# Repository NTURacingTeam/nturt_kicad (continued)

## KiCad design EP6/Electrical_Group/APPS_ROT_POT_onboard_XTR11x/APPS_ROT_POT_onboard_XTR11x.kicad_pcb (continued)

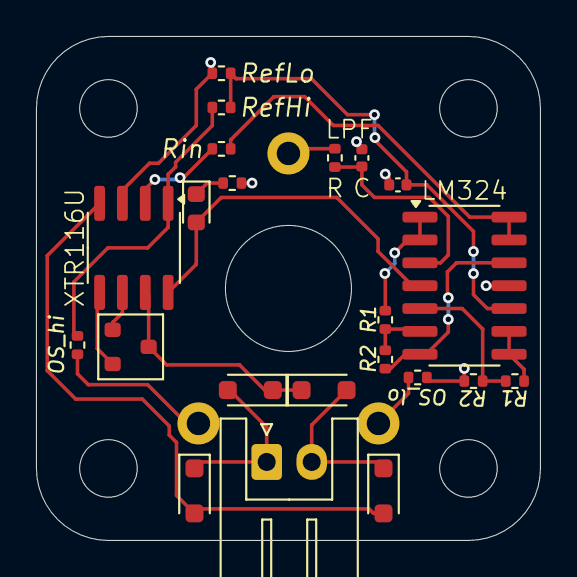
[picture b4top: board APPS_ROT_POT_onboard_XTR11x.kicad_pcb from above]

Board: 2 copper layers, 28.0 x 28.0 mm, 27 parts (1 on the bottom side), 22 nets.

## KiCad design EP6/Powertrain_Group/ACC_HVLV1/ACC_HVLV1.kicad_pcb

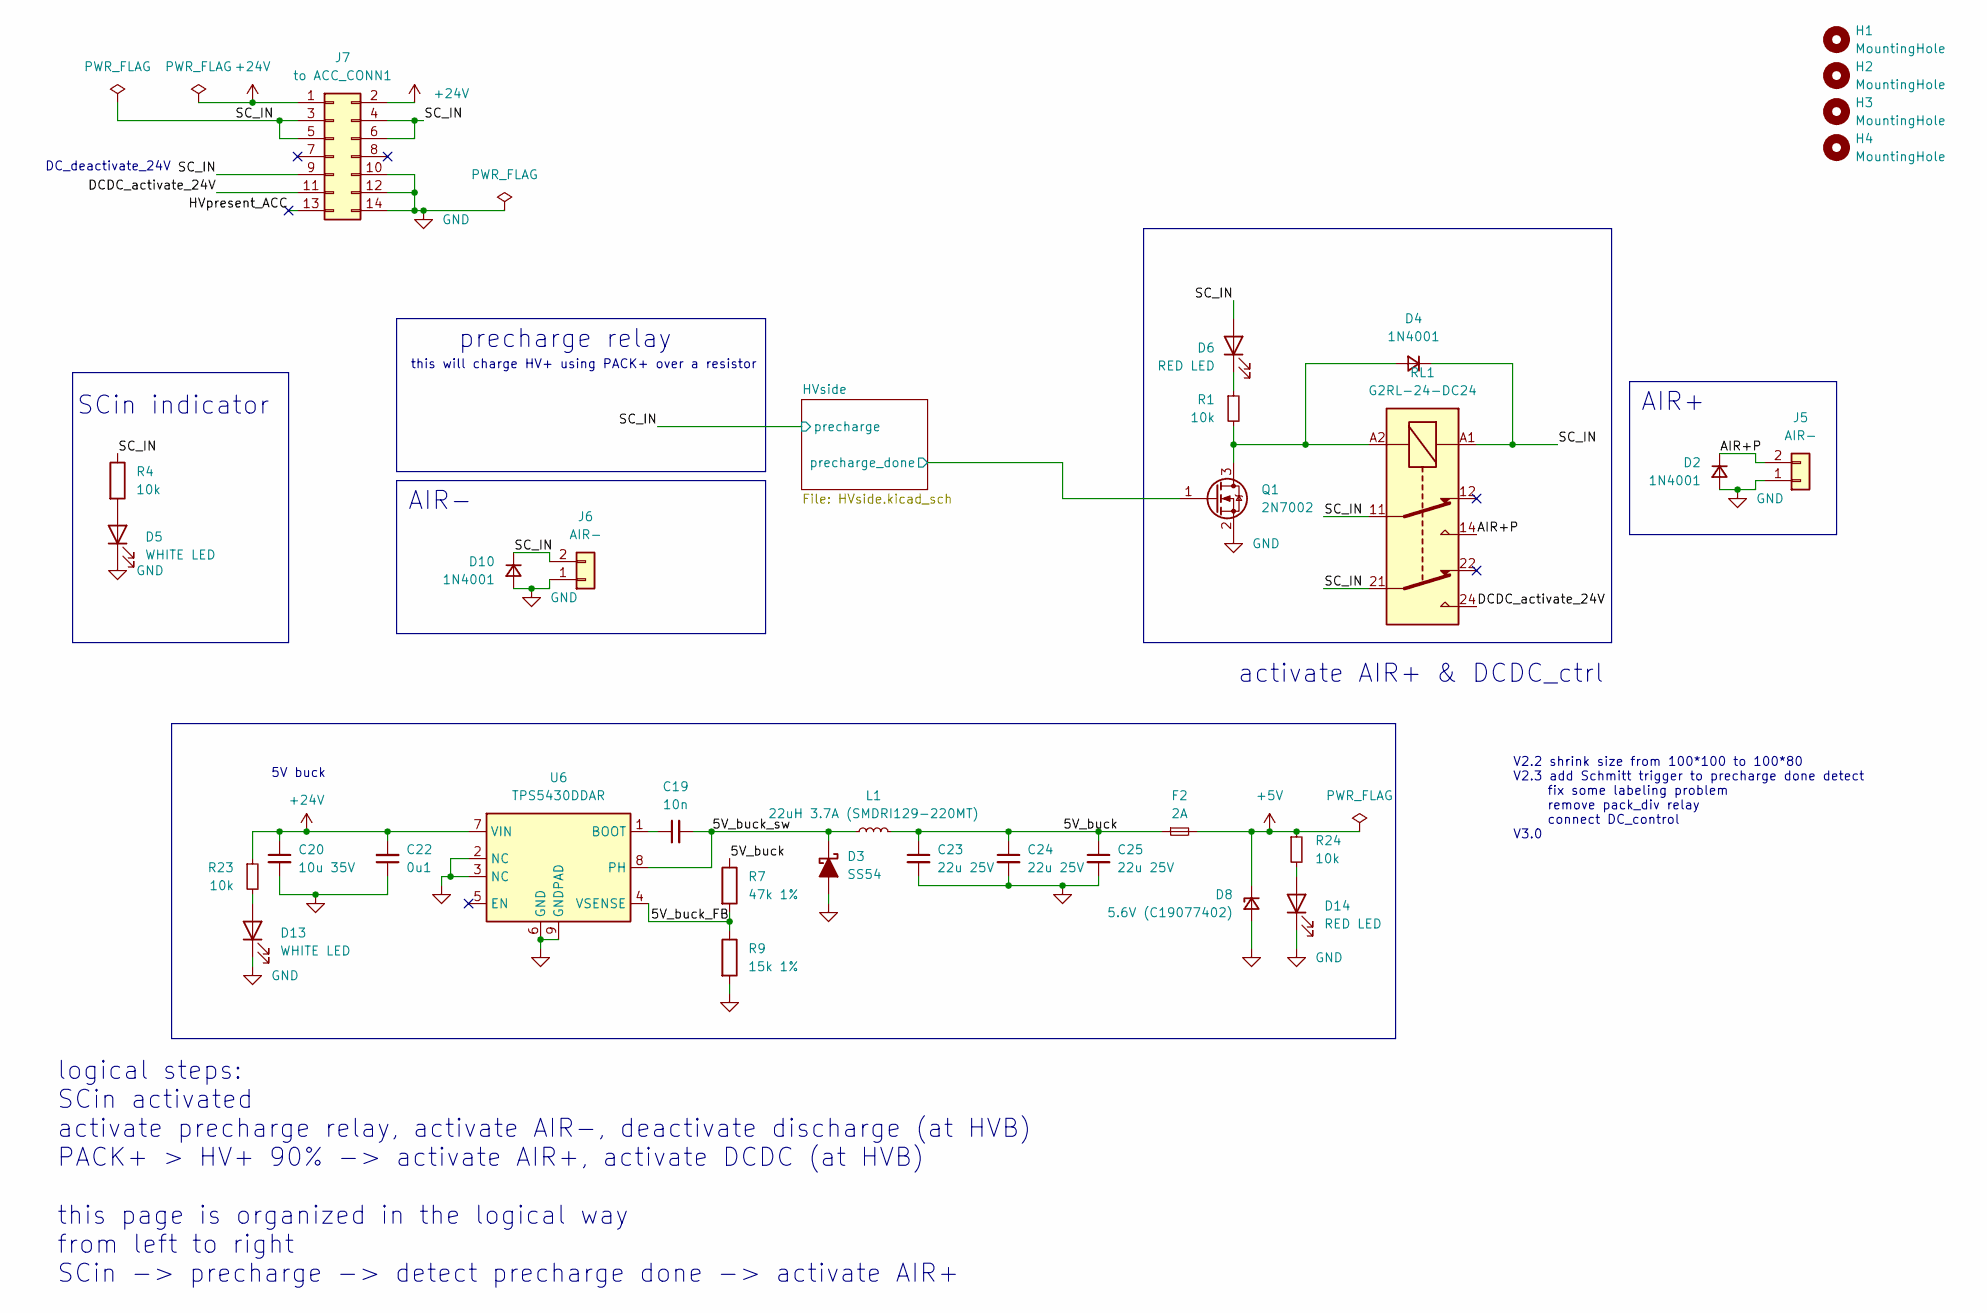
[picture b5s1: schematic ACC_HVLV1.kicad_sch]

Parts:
C19: 10n; C_0603_1608Metric
C20: 10u 35V; C_1206_3216Metric
C22: 0u1; C_0603_1608Metric
C23, C24, C25: 22u 25V; C_1206_3216Metric
D2, D4, D10: 1N4001; D_SOD-123F
D3: SS54; D_SMA
D5, D13: WHITE LED; LED_0805_2012Metric_Pad1.15x1.40mm_HandSolder
D6, D14: RED LED; LED_0805_2012Metric_Pad1.15x1.40mm_HandSolder
D8: 5.6V (C19077402); D_SOD-123
F2: 2A; Fuse_1206_3216Metric
H1, H2, H3, H4: MountingHole; MountingHole_3.2mm_M3
J5, J6: AIR-; JST_VH_B2P-VH-B_1x02_P3.96mm_Vertical
J7: to ACC_CONN1; IDC-Header_2x07_P2.54mm_Vertical
L1: 22uH 3.7A (SMDRI129-220MT); L_Bourns_SRR1260
Q1: 2N7002; SOT-23
R1: 10k; R_0603_1608Metric_Pad0.98x0.95mm_HandSolder
R4: 10k; R_0603_1608Metric
R7: 47k 1%; R_0603_1608Metric
R9: 15k 1%; R_0603_1608Metric
R23, R24: 10k; R_0805_2012Metric_Pad1.20x1.40mm_HandSolder
RL1: G2RL-24-DC24; Relay_DPDT_Omron_G2RL-2
U6: TPS5430DDAR; TI_SO-PowerPAD-8_ThermalVias

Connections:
+5V: D8.1 (K), F2.2, R24.1; also elsewhere on the board
+24V: C20.1, C22.2, J7.1, J7.2, R23.1, U6.7 (VIN)
/5V_buck: C23.1, C24.1, C25.1, F2.1, L1.2, R7.1
/5V_buck_FB: R7.2, R9.1, U6.4 (VSENSE)
/5V_buck_sw: C19.2, D3.1 (K), L1.1, U6.8 (PH)
/AIR+P: D2.1 (K), J5.2, RL1.14
/DCDC_activate_24V: J7.11, RL1.24
/HVpresent_ACC: J7.13
/HVside/precharge_done: Q1.1 (G); also elsewhere on the board
/SC_IN: D4.1 (K), D6.2 (A), D10.1 (K), J6.2, J7.3, J7.4, J7.5, J7.6, J7.9, R4.1, RL1.11, RL1.21, RL1.A1; also elsewhere on the board
GND: C20.2, C22.1, C23.2, C24.2, C25.2, D2.2 (A), D3.2 (A), D5.1 (K), D8.2 (A), D10.2 (A), D13.1 (K), D14.1 (K), J5.1, J6.1, J7.10, J7.12, J7.14, Q1.2 (S), R9.2, U6.2 (NC), U6.3 (NC), U6.6 (GND), U6.9 (GNDPAD); also elsewhere on the board
unnamed: D4.2 (A), Q1.3 (D), R1.2, RL1.A2
unnamed: D5.2 (A), R4.2
unnamed: D6.1 (K), R1.1
unnamed: D13.2 (A), R23.2
unnamed: D14.2 (A), R24.2
unnamed: C19.1, U6.1 (BOOT)

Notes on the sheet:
AIR-
AIR+
V2.2 shrink size from 100*100 to 100*80 V2.3 add Schmitt trigger to precharge done detect fix some labeling problem remove pack_div relay connect DC_control V3.0
5V buck
SCin indicator
this will charge HV+ using PACK+ over a resistor
DC_deactivate_24V
activate AIR+ & DCDC_ctrl
precharge relay
logical steps: SCin activated activate precharge relay, activate AIR-, deactivate discharge (at HVB) PACK+ > HV+ 90% -> activate AIR+, activate DCDC (at HVB) this page is organized in the logical way from left to right SCin -> precharge -> detect precharge done -> activate AIR+

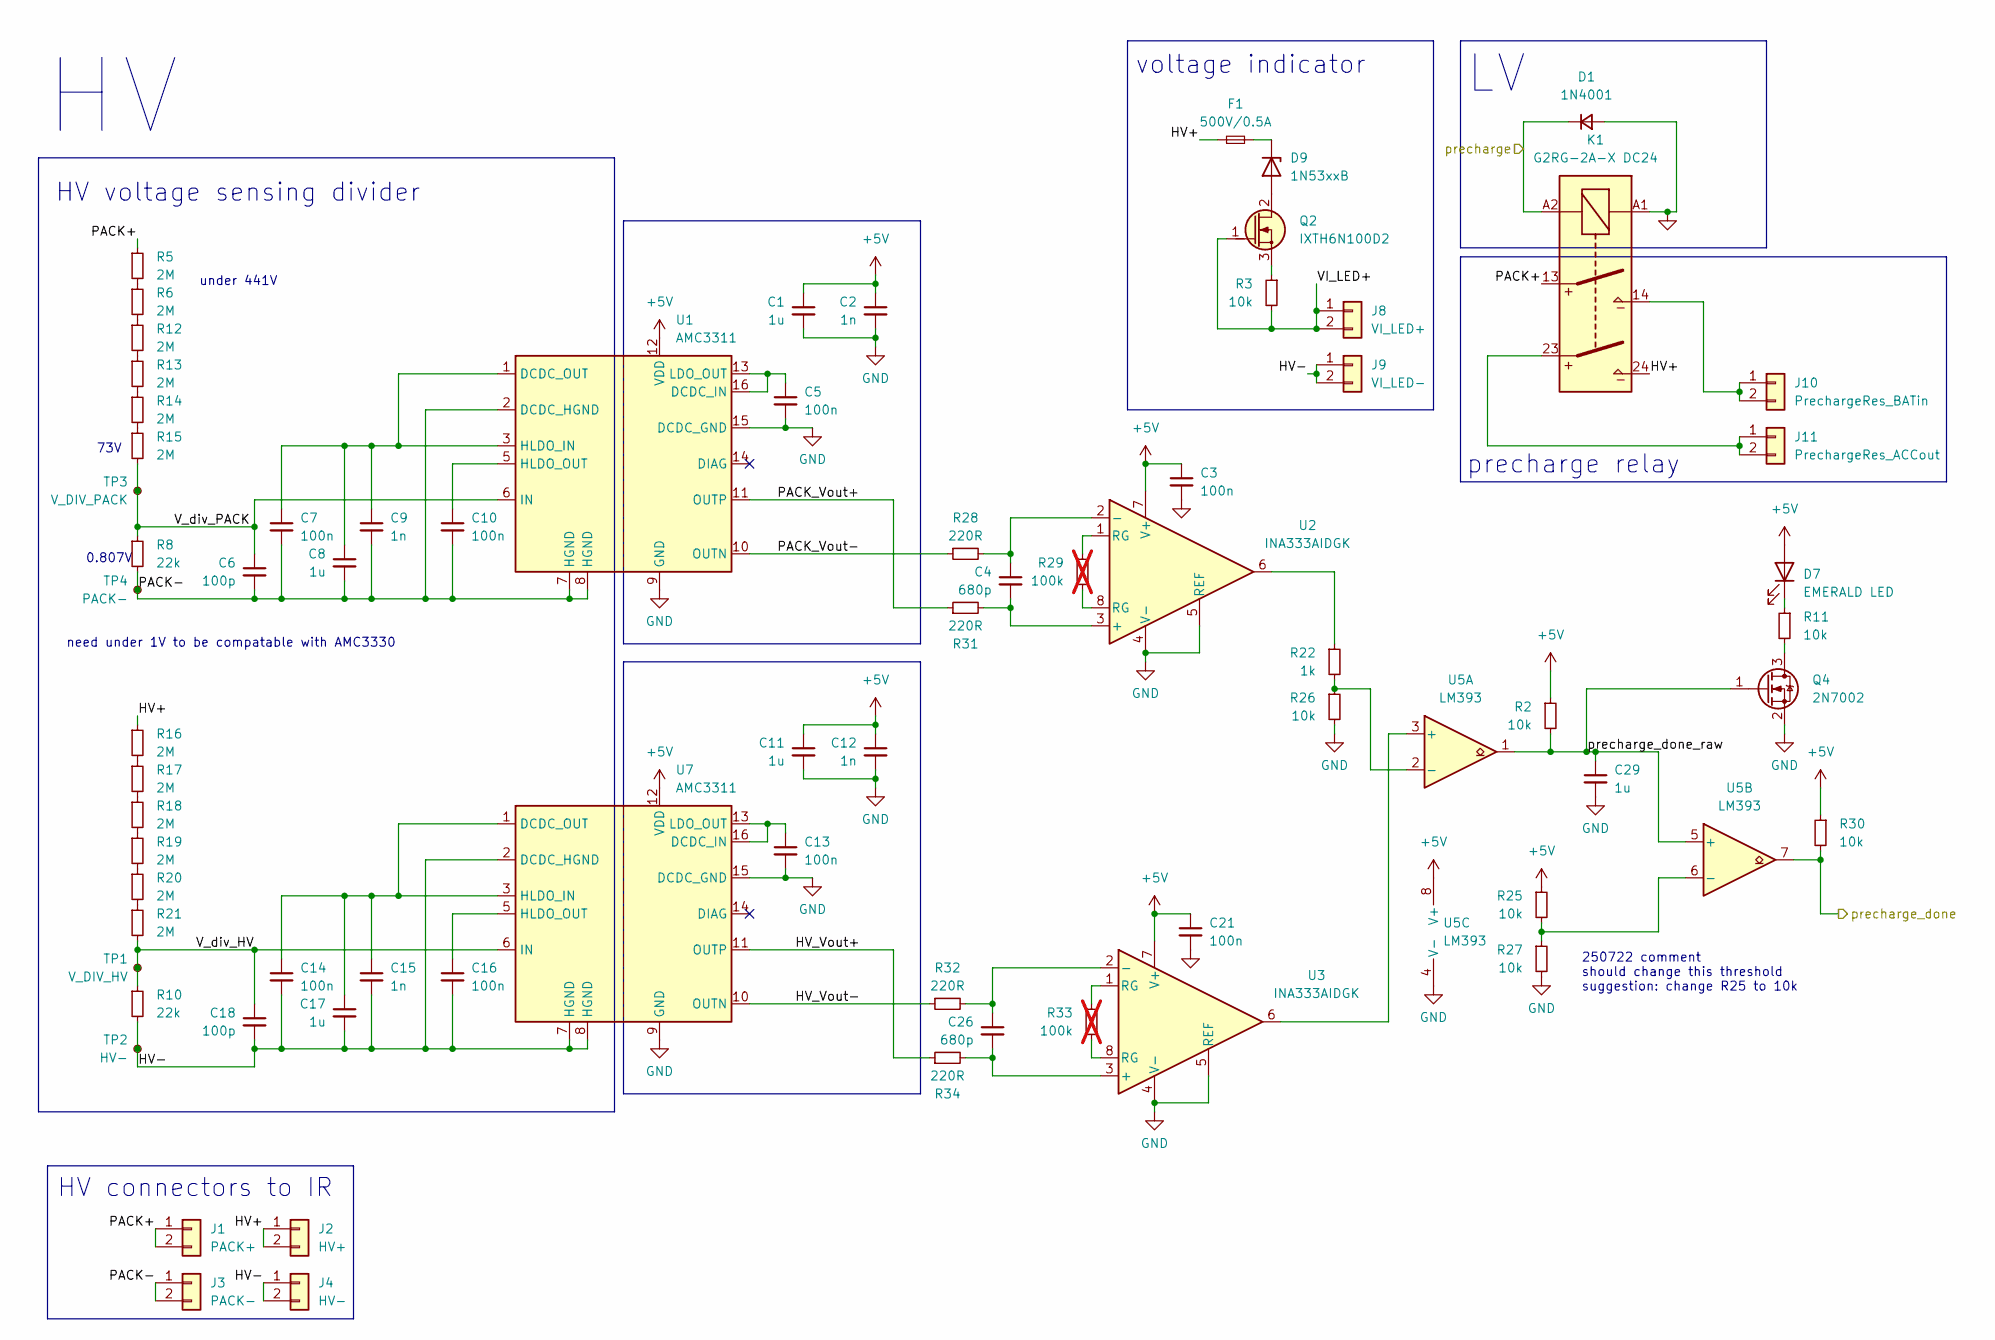
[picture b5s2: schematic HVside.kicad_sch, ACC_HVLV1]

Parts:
C1, C8, C11, C17, C29: 1u; C_0603_1608Metric
C2, C9, C12, C15: 1n; C_0603_1608Metric
C3, C21: 100n; C_0402_1005Metric
C4, C26: 680p; C_0402_1005Metric
C5, C7, C10, C13, C14, C16: 100n; C_0603_1608Metric
C6, C18: 100p; C_0603_1608Metric
D1: 1N4001; D_SOD-123F
D7: EMERALD LED; LED_0805_2012Metric_Pad1.15x1.40mm_HandSolder
D9: 1N53xxB; D_DO-201_P15.24mm_Horizontal
F1: 500V/0.5A; 65600001009; Rating W
J1: PACK+; HRS_DF33C-2P-3.3DSA
J2: HV+; HRS_DF33C-2P-3.3DSA
J3: PACK-; HRS_DF33C-2P-3.3DSA
J4: HV-; HRS_DF33C-2P-3.3DSA
J8: VI_LED+; HRS_DF33C-2P-3.3DSA
J9: VI_LED-; HRS_DF33C-2P-3.3DSA
J10: PrechargeRes_BATin; HRS_DF33C-2P-3.3DSA
J11: PrechargeRes_ACCout; HRS_DF33C-2P-3.3DSA
K1: G2RG-2A-X DC24; Relay_DPST_Omron_G2RL-2A
Q2: IXTH6N100D2; TO-247-3_Vertical
Q4: 2N7002; SOT-23
R2, R11, R25, R26, R27, R30: 10k; R_0603_1608Metric_Pad0.98x0.95mm_HandSolder
R3: 10k; R_0805_2012Metric_Pad1.20x1.40mm_HandSolder
R5, R6, R12, R13, R14, R15, R16, R17, R18, R19, R20, R21: 2M; R_0805_2012Metric_Pad1.20x1.40mm_HandSolder
R8, R10: 22k; R_0805_2012Metric_Pad1.20x1.40mm_HandSolder
R22: 1k; R_0603_1608Metric_Pad0.98x0.95mm_HandSolder
R28, R31, R32, R34: 220R; R_0402_1005Metric
R29, R33: 100k; R_0402_1005Metric; not fitted
TP1: V_DIV_HV; TestPoint_Pad_D2.0mm
TP2: HV-; TestPoint_Pad_D2.0mm
TP3: V_DIV_PACK; TestPoint_Pad_D2.0mm
TP4: PACK-; TestPoint_Pad_D2.0mm
U1, U7: AMC3311; SOIC-16W_7.5x10.3mm_P1.27mm
U2, U3: INA333AIDGK; MSOP-8_3x3mm_P0.65mm
U5: LM393; SOIC-8_3.9x4.9mm_P1.27mm

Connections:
+5V: C1.1, C2.1, C3.1, C11.1, C12.1, C21.1, D7.2 (A), R2.1, R25.1, R30.1, U1.12 (VDD), U2.7 (V+), U3.7 (V+), U5.8 (V+), U7.12 (VDD); also elsewhere on the board
/HVside/HV+: F1.2, J2.1, J2.2, K1.24, R16.1
/HVside/HV-: C14.2, C15.2, C16.2, C17.2, C18.2, J4.1, J4.2, J9.1, J9.2, R10.2, TP2.1, U7.2 (DCDC_HGND), U7.7 (HGND), U7.8 (HGND)
/HVside/HV_Vout+: R34.1, U7.11 (OUTP)
/HVside/HV_Vout-: R32.1, U7.10 (OUTN)
/HVside/PACK+: J1.1, J1.2, K1.13, R5.1
/HVside/PACK-: C6.2, C7.2, C8.2, C9.2, C10.2, J3.1, J3.2, R8.2, TP4.1, U1.2 (DCDC_HGND), U1.7 (HGND), U1.8 (HGND)
/HVside/PACK_Vout+: R31.1, U1.11 (OUTP)
/HVside/PACK_Vout-: R28.1, U1.10 (OUTN)
/HVside/VI_LED+: J8.1, J8.2, Q2.1 (G), R3.2
/HVside/V_div_HV: C18.1, R10.1, R21.2, TP1.1, U7.6 (IN)
/HVside/V_div_PACK: C6.1, R8.1, R15.2, TP3.1, U1.6 (IN)
/HVside/precharge_done: R30.2, U5.7; also elsewhere on the board
/HVside/precharge_done_raw: C29.1, Q4.1 (G), R2.2, U5.1, U5.5 (+)
/SC_IN: D1.1 (K), K1.A2; also elsewhere on the board
GND: C1.2, C2.2, C3.2, C5.2, C11.2, C12.2, C13.2, C21.2, C29.2, D1.2 (A), K1.A1, Q4.2 (S), R26.2, R27.2, U1.9 (GND), U1.15 (DCDC_GND), U2.4 (V-), U2.5 (REF), U3.4 (V-), U3.5 (REF), U5.4 (V-), U7.9 (GND), U7.15 (DCDC_GND); also elsewhere on the board
unnamed: D7.1 (K), R11.1
unnamed: D9.2 (A), Q2.2 (D)
unnamed: D9.1 (K), F1.1
unnamed: J10.1, J10.2, K1.14
unnamed: J11.1, J11.2, K1.23
unnamed: Q2.3 (S), R3.1
unnamed: Q4.3 (D), R11.2
unnamed: R5.2, R6.1
unnamed: R6.2, R12.1
unnamed: R12.2, R13.1
unnamed: R13.2, R14.1
unnamed: R14.2, R15.1
unnamed: R16.2, R17.1
unnamed: R17.2, R18.1
unnamed: R18.2, R19.1
unnamed: R19.2, R20.1
unnamed: R20.2, R21.1
unnamed: R22.1, U2.6
unnamed: R29.1, U2.8 (RG)
unnamed: R29.2, U2.1 (RG)
unnamed: R33.1, U3.8 (RG)
unnamed: R33.2, U3.1 (RG)
unnamed: C5.1, U1.13 (LDO_OUT), U1.16 (DCDC_IN)
unnamed: C7.1, C8.1, C9.1, U1.1 (DCDC_OUT), U1.3 (HLDO_IN)
unnamed: C10.1, U1.5 (HLDO_OUT)
unnamed: C4.2, R31.2, U2.3 (+)
unnamed: C4.1, R28.2, U2.2 (-)
unnamed: C26.2, R34.2, U3.3 (+)
unnamed: C26.1, R32.2, U3.2 (-)
unnamed: U3.6, U5.3 (+)
unnamed: R22.2, R26.1, U5.2 (-)
unnamed: R25.2, R27.1, U5.6 (-)
unnamed: C13.1, U7.13 (LDO_OUT), U7.16 (DCDC_IN)
unnamed: C14.1, C15.1, C17.1, U7.1 (DCDC_OUT), U7.3 (HLDO_IN)
unnamed: C16.1, U7.5 (HLDO_OUT)

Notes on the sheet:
250722 comment should change this threshold suggestion: change R25 to 10k
voltage indicator
HV voltage sensing divider
HV connectors to IR
under 441V
73V
need under 1V to be compatable with AMC3330
precharge relay
0.807V

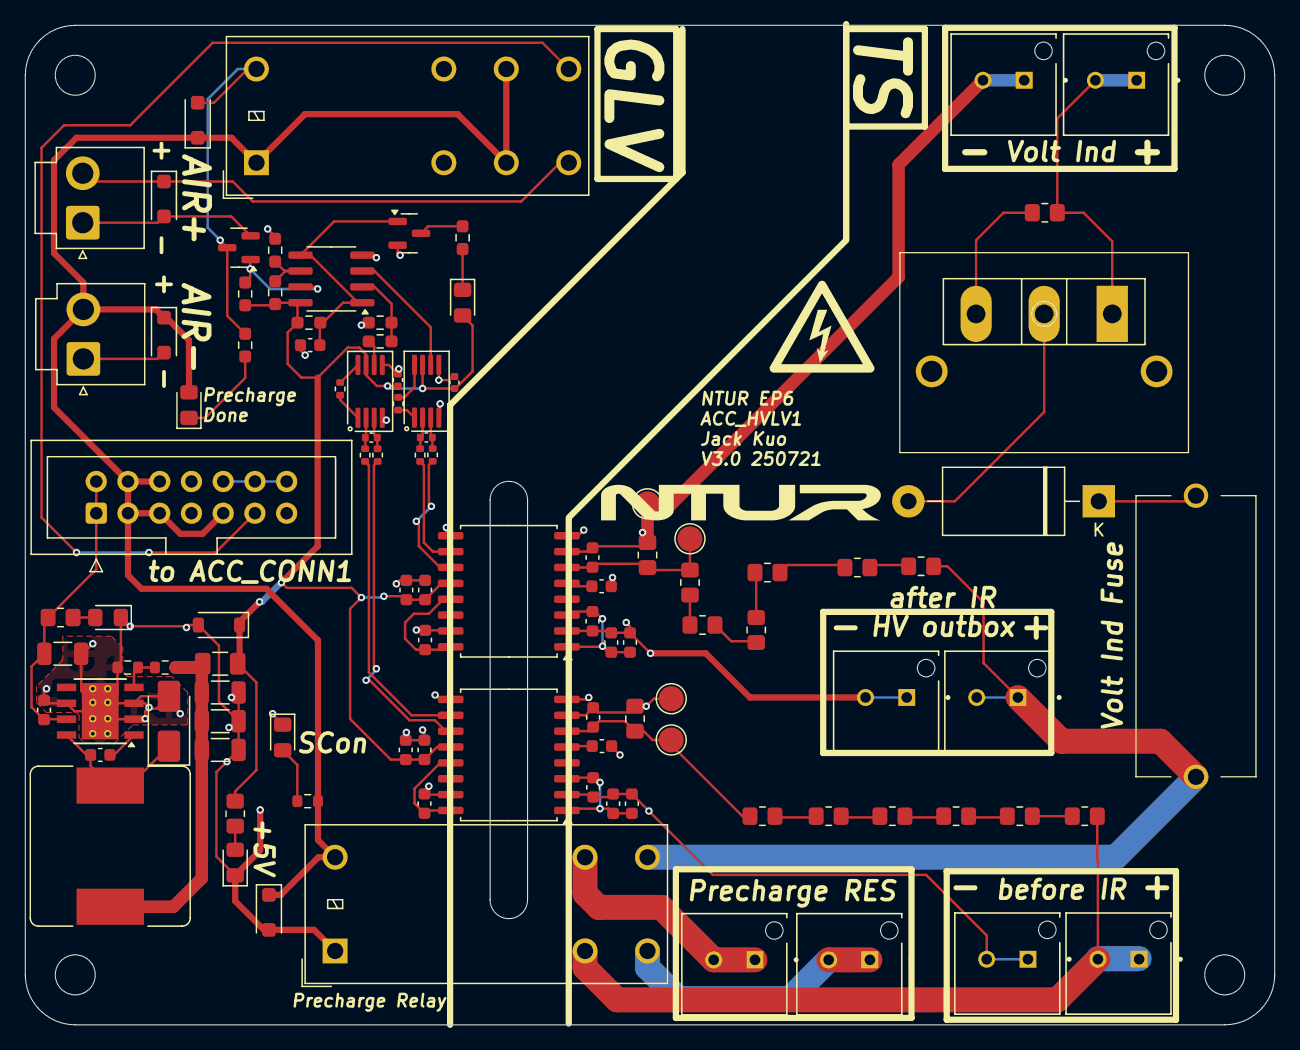
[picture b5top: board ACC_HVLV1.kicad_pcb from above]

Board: 2 copper layers, 100.0 x 80.0 mm, 106 parts (0 on the bottom side), 63 nets.

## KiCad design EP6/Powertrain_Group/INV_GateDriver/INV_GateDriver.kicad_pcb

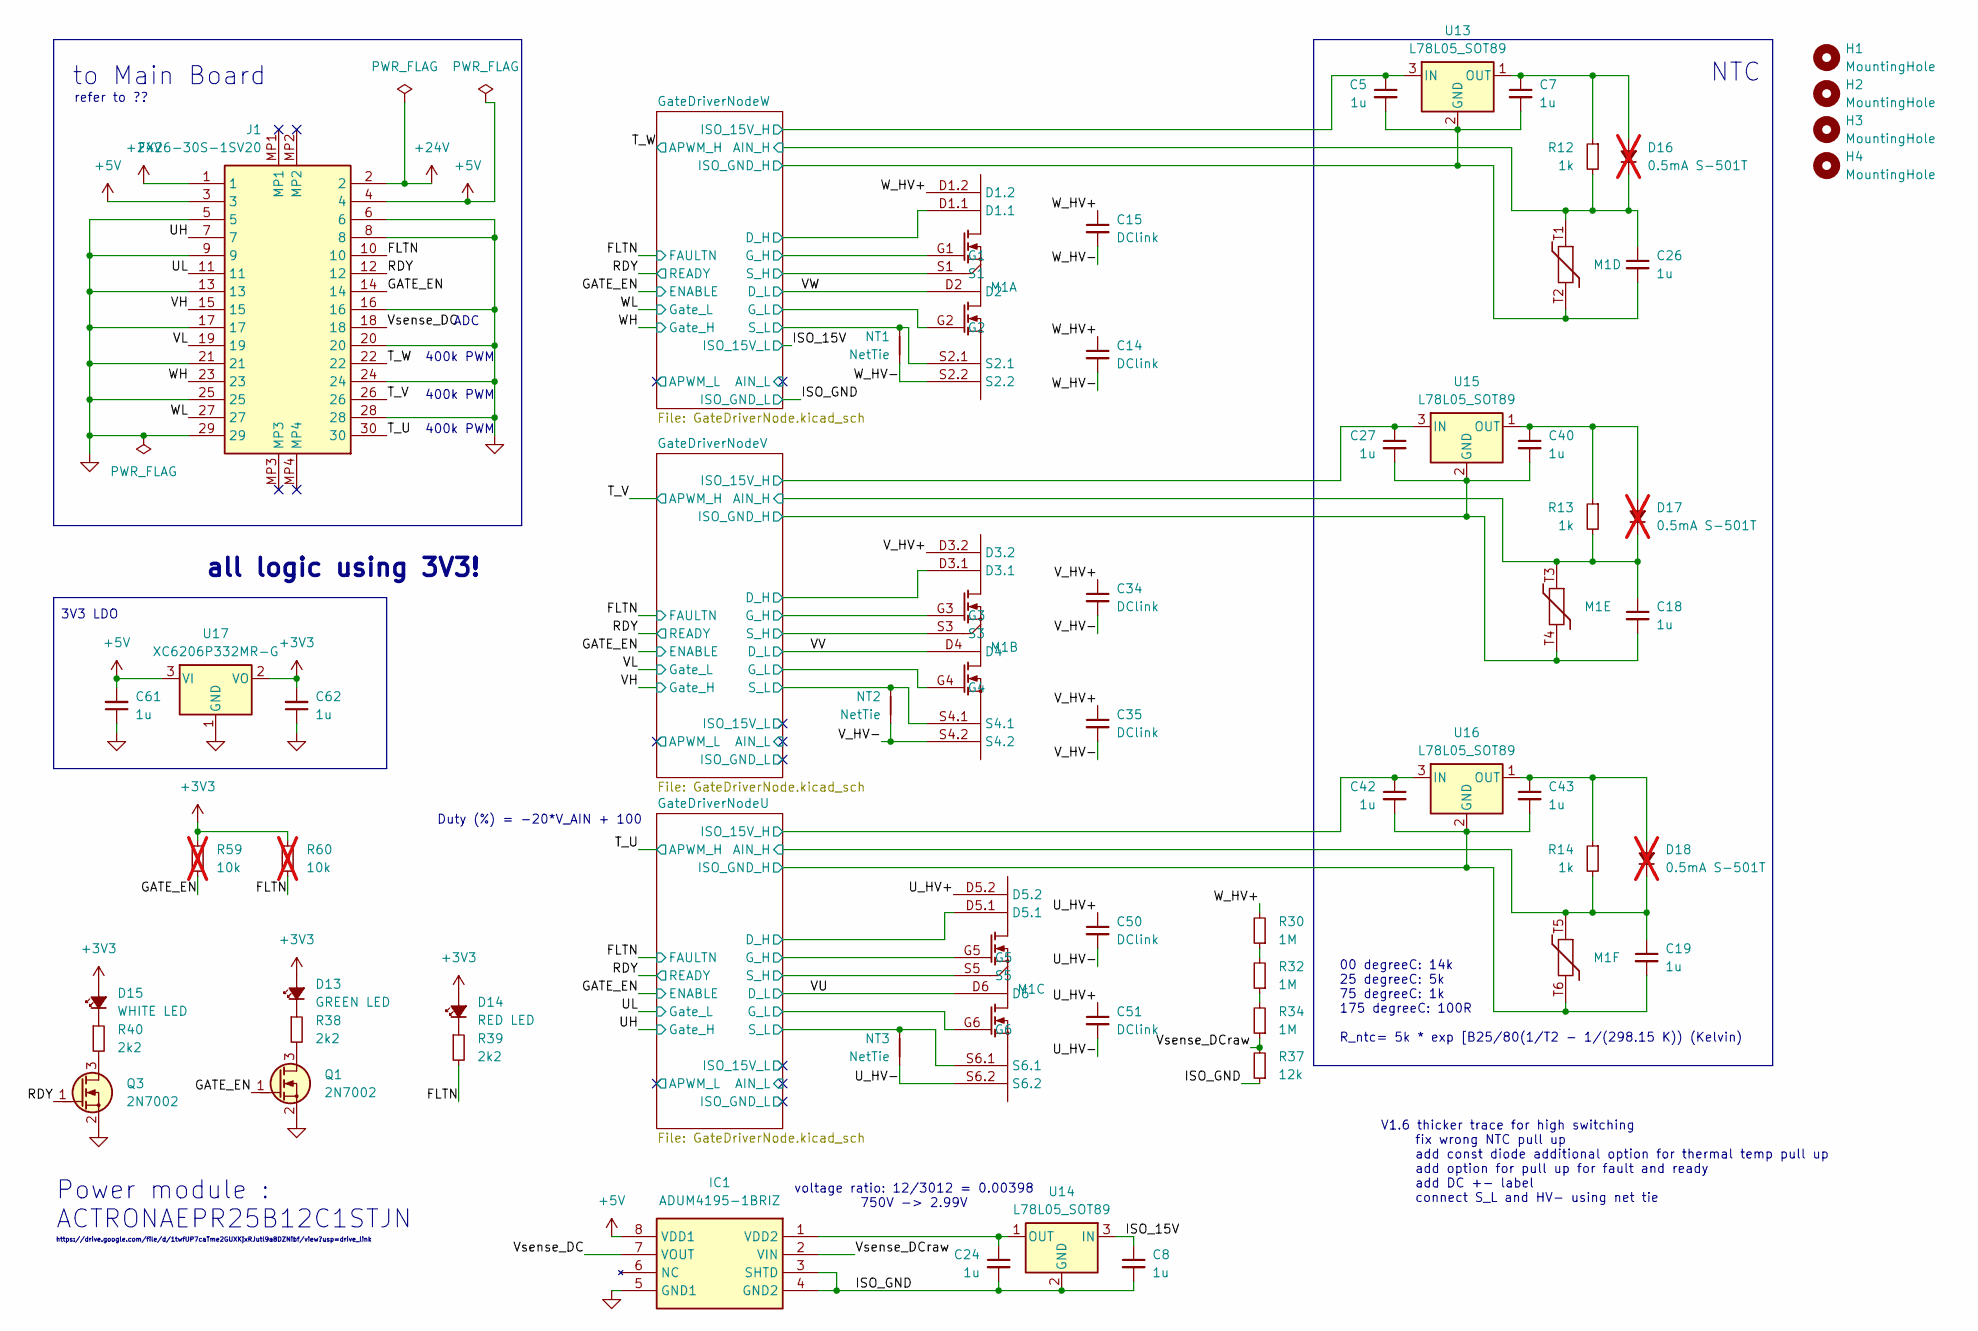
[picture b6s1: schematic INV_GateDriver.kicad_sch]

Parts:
C5, C7, C8, C18, C19, C24, C26, C27, C40, C42, C43: 1u; C_0603_1608Metric
C14, C15, C34, C35, C50, C51: DClink; B58035U5205M062
C61, C62: 1u; C_0402_1005Metric
D13: GREEN LED; LED_0805_2012Metric
D14: RED LED; LED_0805_2012Metric
D15: WHITE LED; LED_0805_2012Metric
D16, D17, D18: 0.5mA S-501T; D_1206_3216Metric; not fitted
H1, H2, H3, H4: MountingHole; MountingHole_3.2mm_M3
IC1: ADUM4195-1BRIZ; SOIC127P1031X265-8N; Manufacturer_Part_Number ADUM4195-1BRIZ; Mouser Part Number 584-ADUM4195-1BRIZ
J1: FX26-30S-1SV20; FX2630S1SV20; Mouser Part Number 798-FX2630S1SV20
M1: InverterSiCModule_HybridPack
NT1, NT2, NT3: NetTie; NetTie-2_SMD_Pad2.0mm
Q1, Q3: 2N7002; SOT-23
R12, R13, R14: 1k; R_0603_1608Metric
R30, R32, R34: 1M; R_1206_3216Metric
R37: 12k; R_0805_2012Metric
R38, R39, R40: 2k2; R_0402_1005Metric
R59, R60: 10k; R_0402_1005Metric; not fitted
U13, U14, U15, U16: L78L05_SOT89; SOT-89-3
U17: XC6206P332MR-G; SOT-23-3

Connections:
+3V3: C62.2, D13.2 (A), D14.2 (A), D15.2 (A), R59.1, R60.1, U17.2 (VO); also elsewhere on the board
+5V: C61.2, IC1.8 (VDD1), J1.3, J1.4, U17.3 (VI)
+24V: J1.1, J1.2; also elsewhere on the board
/FLTN: J1.10, R39.2, R60.2; also elsewhere on the board
/GATE_EN: J1.14, Q1.1 (G), R59.2; also elsewhere on the board
/GateDriverNodeU/0V_H: C19.2, C42.2, C43.2, M1.S5, M1.T6, U16.2 (GND); also elsewhere on the board
/GateDriverNodeU/0V_L: M1.S6.1, NT3.2; also elsewhere on the board
/GateDriverNodeU/+V_H: C42.1, U16.3 (IN); also elsewhere on the board
/GateDriverNodeU/AIN_H: C19.1, D18.1 (K), M1.T5, R14.2; also elsewhere on the board
/GateDriverNodeU/D_H: M1.D5.1; also elsewhere on the board
/GateDriverNodeU/G_H: M1.G5; also elsewhere on the board
/GateDriverNodeU/G_L: M1.G6; also elsewhere on the board
/GateDriverNodeV/0V_H: C18.2, C27.2, C40.2, M1.S3, M1.T4, U15.2 (GND); also elsewhere on the board
/GateDriverNodeV/0V_L: M1.S4.1, NT2.2; also elsewhere on the board
/GateDriverNodeV/+V_H: C27.1, U15.3 (IN); also elsewhere on the board
/GateDriverNodeV/AIN_H: C18.1, D17.1 (K), M1.T3, R13.2; also elsewhere on the board
/GateDriverNodeV/D_H: M1.D3.1; also elsewhere on the board
/GateDriverNodeV/G_H: M1.G3; also elsewhere on the board
/GateDriverNodeV/G_L: M1.G4; also elsewhere on the board
/GateDriverNodeW/0V_H: C5.2, C7.2, C26.2, M1.S1, M1.T2, U13.2 (GND); also elsewhere on the board
/GateDriverNodeW/+V_H: C5.1, U13.3 (IN); also elsewhere on the board
/GateDriverNodeW/AIN_H: C26.1, D16.1 (K), M1.T1, R12.2; also elsewhere on the board
/GateDriverNodeW/D_H: M1.D1.1; also elsewhere on the board
/GateDriverNodeW/G_H: M1.G1; also elsewhere on the board
/GateDriverNodeW/G_L: M1.G2; also elsewhere on the board
/ISO_15V: C8.1, U14.3 (IN); also elsewhere on the board
/ISO_GND: C8.2, C24.2, IC1.3 (SHTD), IC1.4 (GND2), M1.S2.1, NT1.2, R37.1, U14.2 (GND); also elsewhere on the board
/RDY: J1.12, Q3.1 (G); also elsewhere on the board
/T_U: J1.30; also elsewhere on the board
/T_V: J1.26; also elsewhere on the board
/T_W: J1.22; also elsewhere on the board
/UH: J1.7; also elsewhere on the board
/UL: J1.11; also elsewhere on the board
/U_HV+: C50.1, C51.1, M1.D5.2
/U_HV-: C50.2, C51.2, M1.S6.2, NT3.1
/VH: J1.15; also elsewhere on the board
/VL: J1.19; also elsewhere on the board
/VU: M1.D6; also elsewhere on the board
/VV: M1.D4; also elsewhere on the board
/VW: M1.D2; also elsewhere on the board
/V_HV+: C34.1, C35.1, M1.D3.2
/V_HV-: C34.2, C35.2, M1.S4.2, NT2.1
/Vsense_DC: IC1.7 (VOUT), J1.18
/Vsense_DCraw: IC1.2 (VIN), R34.1, R37.2
/WH: J1.23; also elsewhere on the board
/WL: J1.27; also elsewhere on the board
/W_HV+: C14.1, C15.1, M1.D1.2, R30.2
/W_HV-: C14.2, C15.2, M1.S2.2, NT1.1
GND: C61.1, C62.1, IC1.5 (GND1), J1.5, J1.6, J1.8, J1.9, J1.13, J1.16, J1.17, J1.20, J1.21, J1.24, J1.25, J1.28, J1.29, Q1.2 (S), Q3.2 (S), U17.1 (GND); also elsewhere on the board
unnamed: D13.1 (K), R38.1
unnamed: D14.1 (K), R39.1
unnamed: D15.1 (K), R40.1
unnamed: C7.1, D16.2 (A), R12.1, U13.1 (OUT)
unnamed: C40.1, D17.2 (A), R13.1, U15.1 (OUT)
unnamed: C43.1, D18.2 (A), R14.1, U16.1 (OUT)
unnamed: C24.1, IC1.1 (VDD2), U14.1 (OUT)
unnamed: Q1.3 (D), R38.2
unnamed: Q3.3 (D), R40.2
unnamed: R30.1, R32.2
unnamed: R32.1, R34.2

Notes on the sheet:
Power module : ACTRONAEPR25B12C1STJN
NTC
all logic using 3V3!
V1.6 thicker trace for high switching fix wrong NTC pull up add const diode additional option for thermal temp pull up add option for pull up for fault and ready add DC +- label connect S_L and HV- using net tie
Duty (%) = -20*V_AIN + 100
400k PWM
refer to ??
to Main Board
ADC
3V3 LDO
00 degreeC: 14k 25 degreeC: 5k 75 degreeC: 1k 175 degreeC: 100R R_ntc= 5k * exp [B25/80(1/T2 - 1/(298.15 K)) (Kelvin)
voltage ratio: 12/3012 = 0.00398 750V -> 2.99V
https://drive.google.com/file/d/1twfUP7caTme2GUXKjxRJutl9a8DZNibf/view?usp=drive_link

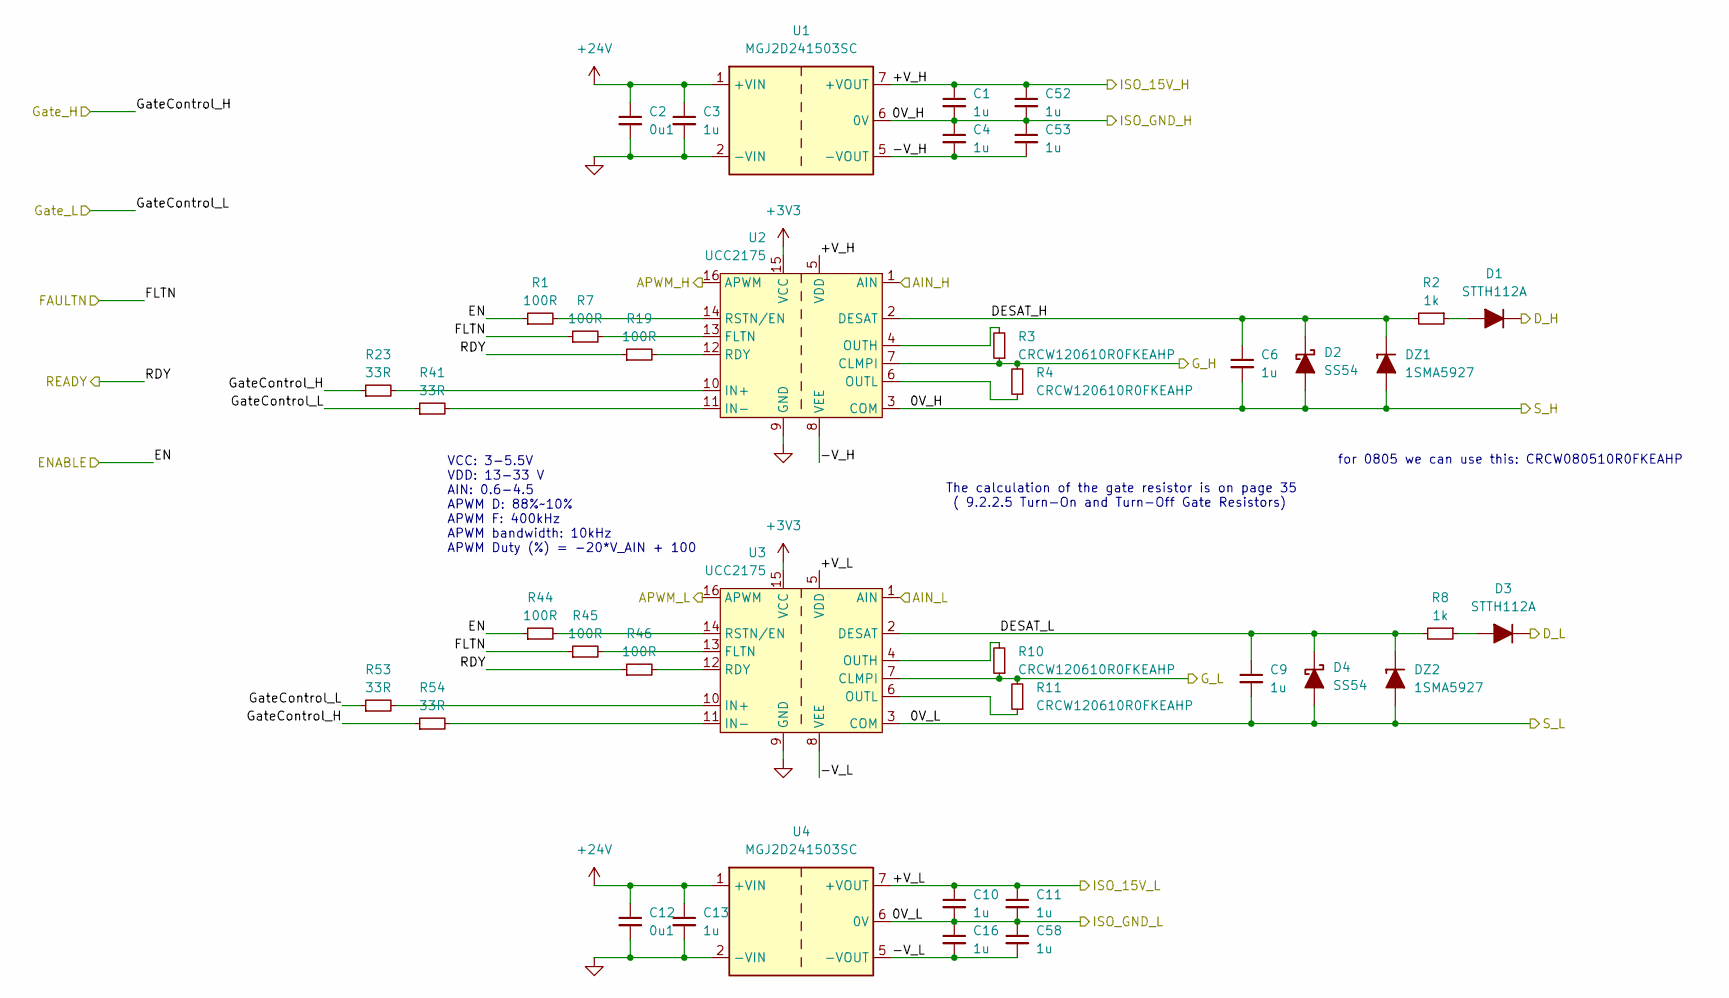
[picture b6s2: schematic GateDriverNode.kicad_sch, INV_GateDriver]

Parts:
C1, C4, C10, C11, C16, C52, C53, C58: 1u; C_1206_3216Metric
C2, C12: 0u1; C_0603_1608Metric
C3, C6, C9, C13: 1u; C_0603_1608Metric
D1, D3: STTH112A; D_SMA
D2, D4: SS54; D_SMA
DZ1, DZ2: 1SMA5927; D_SMA
R1, R7, R19, R44, R45, R46: 100R; R_0402_1005Metric
R2, R8: 1k; R_0603_1608Metric
R3, R4, R10, R11: CRCW120610R0FKEAHP; R_1206_3216Metric
R23, R41, R53, R54: 33R; R_0402_1005Metric
U1, U4: MGJ2D241503SC; Converter_DCDC_Murata_MGJ2DxxxxxxSC_THT
U2, U3: UCC2175; SOIC-16W_7.5x10.3mm_P1.27mm

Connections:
+3V3: U2.15 (VCC), U3.15 (VCC); also elsewhere on the board
+24V: C2.1, C3.1, C12.1, C13.1, U1.1 (+VIN), U4.1 (+VIN); also elsewhere on the board
/FLTN: R7.1, R45.1; also elsewhere on the board
/GATE_EN: R1.1, R44.1; also elsewhere on the board
/GateDriverNodeW/0V_H: C1.2, C4.1, C6.2, C52.2, C53.1, D2.2 (A), DZ1.2 (A), U1.6 (0V), U2.3 (COM); also elsewhere on the board
/GateDriverNodeW/+V_H: C1.1, C52.1, U1.7 (+VOUT), U2.5 (VDD); also elsewhere on the board
/GateDriverNodeW/-V_H: C4.2, C53.2, U1.5 (-VOUT), U2.8 (VEE)
/GateDriverNodeW/-V_L: C16.2, C58.2, U3.8 (VEE), U4.5 (-VOUT)
/GateDriverNodeW/AIN_H: U2.1 (AIN); also elsewhere on the board
/GateDriverNodeW/AIN_L: U3.1 (AIN)
/GateDriverNodeW/APWM_L: U3.16 (APWM)
/GateDriverNodeW/DESAT_H: C6.1, D2.1 (K), DZ1.1 (K), R2.2, U2.2 (DESAT)
/GateDriverNodeW/DESAT_L: C9.1, D4.1 (K), DZ2.1 (K), R8.2, U3.2 (DESAT)
/GateDriverNodeW/D_H: D1.1 (K); also elsewhere on the board
/GateDriverNodeW/G_H: R3.1, R4.2, U2.7 (CLMPI); also elsewhere on the board
/GateDriverNodeW/G_L: R10.1, R11.2, U3.7 (CLMPI); also elsewhere on the board
/ISO_15V: C10.1, C11.1, U3.5 (VDD), U4.7 (+VOUT); also elsewhere on the board
/ISO_GND: C9.2, C10.2, C11.2, C16.1, C58.1, D4.2 (A), DZ2.2 (A), U3.3 (COM), U4.6 (0V); also elsewhere on the board
/RDY: R19.1, R46.1; also elsewhere on the board
/T_W: U2.16 (APWM); also elsewhere on the board
/VW: D3.1 (K); also elsewhere on the board
/WH: R23.1, R54.1; also elsewhere on the board
/WL: R41.1, R53.1; also elsewhere on the board
GND: C2.2, C3.2, C12.2, C13.2, U1.2 (-VIN), U2.9 (GND), U3.9 (GND), U4.2 (-VIN); also elsewhere on the board
unnamed: D1.2 (A), R2.1
unnamed: D3.2 (A), R8.1
unnamed: R7.2, U2.13 (FLTN)
unnamed: R23.2, U2.10 (IN+)
unnamed: R41.2, U2.11 (IN-)
unnamed: R3.2, U2.4 (OUTH)
unnamed: R4.1, U2.6 (OUTL)
unnamed: R19.2, U2.12 (RDY)
unnamed: R1.2, U2.14 (RSTN/EN)
unnamed: R45.2, U3.13 (FLTN)
unnamed: R53.2, U3.10 (IN+)
unnamed: R54.2, U3.11 (IN-)
unnamed: R10.2, U3.4 (OUTH)
unnamed: R11.1, U3.6 (OUTL)
unnamed: R46.2, U3.12 (RDY)
unnamed: R44.2, U3.14 (RSTN/EN)

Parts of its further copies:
C20, C23, C29, C30, C33, C36, C39, C45, C46, C49, C54, C55, C56, C57, C59, C60: 1u; C_1206_3216Metric
C21, C31, C37, C47: 0u1; C_0603_1608Metric
C22, C25, C28, C32, C38, C41, C44, C48: 1u; C_0603_1608Metric
D5, D7, D9, D11: STTH112A; D_SMA
D6, D8, D10, D12: SS54; D_SMA
DZ3, DZ4, DZ5, DZ6: 1SMA5927; D_SMA
R5, R6, R9, R15, R20, R21, R47, R48, R49, R50, R51, R52: 100R; R_0402_1005Metric
R16, R22, R27, R33: 1k; R_0603_1608Metric
R26, R31, R42, R43, R55, R56, R57, R58: 33R; R_0402_1005Metric
U5, U8, U9, U12: MGJ2D241503SC; Converter_DCDC_Murata_MGJ2DxxxxxxSC_THT
U6, U7, U10, U11: UCC2175; SOIC-16W_7.5x10.3mm_P1.27mm

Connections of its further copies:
+3V3: U6.15 (VCC), U7.15 (VCC), U10.15 (VCC), U11.15 (VCC); also elsewhere on the board
+24V: C21.1, C22.1, C31.1, C32.1, C37.1, C38.1, C47.1, C48.1, U5.1 (+VIN), U8.1 (+VIN), U9.1 (+VIN), U12.1 (+VIN); also elsewhere on the board
/FLTN: R9.1, R15.1, R48.1, R51.1; also elsewhere on the board
/GATE_EN: R5.1, R6.1, R47.1, R50.1; also elsewhere on the board
/GateDriverNodeU/0V_H: C36.2, C39.1, C41.2, C56.2, C57.1, D10.2 (A), DZ5.2 (A), U9.6 (0V), U10.3 (COM); also elsewhere on the board
/GateDriverNodeU/0V_L: C44.2, C45.2, C46.2, C49.1, C60.1, D12.2 (A), DZ6.2 (A), U11.3 (COM), U12.6 (0V); also elsewhere on the board
/GateDriverNodeU/+V_H: C36.1, C56.1, U9.7 (+VOUT), U10.5 (VDD); also elsewhere on the board
/GateDriverNodeU/+V_L: C45.1, C46.1, U11.5 (VDD), U12.7 (+VOUT)
/GateDriverNodeU/-V_H: C39.2, C57.2, U9.5 (-VOUT), U10.8 (VEE)
/GateDriverNodeU/-V_L: C49.2, C60.2, U11.8 (VEE), U12.5 (-VOUT)
/GateDriverNodeU/AIN_H: U10.1 (AIN); also elsewhere on the board
/GateDriverNodeU/AIN_L: U11.1 (AIN)
/GateDriverNodeU/APWM_L: U11.16 (APWM)
/GateDriverNodeU/DESAT_H: C41.1, D10.1 (K), DZ5.1 (K), R27.2, U10.2 (DESAT)
/GateDriverNodeU/DESAT_L: C44.1, D12.1 (K), DZ6.1 (K), R33.2, U11.2 (DESAT)
/GateDriverNodeU/D_H: D9.1 (K); also elsewhere on the board
/GateDriverNodeU/G_H: U10.7 (CLMPI); also elsewhere on the board
/GateDriverNodeU/G_L: U11.7 (CLMPI); also elsewhere on the board
/GateDriverNodeV/0V_H: C20.2, C23.1, C25.2, C54.2, C55.1, D6.2 (A), DZ3.2 (A), U5.6 (0V), U6.3 (COM); also elsewhere on the board
/GateDriverNodeV/0V_L: C28.2, C29.2, C30.2, C33.1, C59.1, D8.2 (A), DZ4.2 (A), U7.3 (COM), U8.6 (0V); also elsewhere on the board
/GateDriverNodeV/+V_H: C20.1, C54.1, U5.7 (+VOUT), U6.5 (VDD); also elsewhere on the board
/GateDriverNodeV/+V_L: C29.1, C30.1, U7.5 (VDD), U8.7 (+VOUT)
/GateDriverNodeV/-V_H: C23.2, C55.2, U5.5 (-VOUT), U6.8 (VEE)
/GateDriverNodeV/-V_L: C33.2, C59.2, U7.8 (VEE), U8.5 (-VOUT)
/GateDriverNodeV/AIN_H: U6.1 (AIN); also elsewhere on the board
/GateDriverNodeV/AIN_L: U7.1 (AIN)
/GateDriverNodeV/APWM_L: U7.16 (APWM)
/GateDriverNodeV/DESAT_H: C25.1, D6.1 (K), DZ3.1 (K), R16.2, U6.2 (DESAT)
/GateDriverNodeV/DESAT_L: C28.1, D8.1 (K), DZ4.1 (K), R22.2, U7.2 (DESAT)
/GateDriverNodeV/D_H: D5.1 (K); also elsewhere on the board
/GateDriverNodeV/G_H: U6.7 (CLMPI); also elsewhere on the board
/GateDriverNodeV/G_L: U7.7 (CLMPI); also elsewhere on the board
/RDY: R20.1, R21.1, R49.1, R52.1; also elsewhere on the board
/T_U: U10.16 (APWM); also elsewhere on the board
/T_V: U6.16 (APWM); also elsewhere on the board
/UH: R31.1, R58.1; also elsewhere on the board
/UL: R43.1, R57.1; also elsewhere on the board
/VH: R26.1, R56.1; also elsewhere on the board
/VL: R42.1, R55.1; also elsewhere on the board
/VU: D11.1 (K); also elsewhere on the board
/VV: D7.1 (K); also elsewhere on the board
GND: C21.2, C22.2, C31.2, C32.2, C37.2, C38.2, C47.2, C48.2, U5.2 (-VIN), U6.9 (GND), U7.9 (GND), U8.2 (-VIN), U9.2 (-VIN), U10.9 (GND), U11.9 (GND), U12.2 (-VIN); also elsewhere on the board
unnamed: D5.2 (A), R16.1
unnamed: D7.2 (A), R22.1
unnamed: D9.2 (A), R27.1
unnamed: D11.2 (A), R33.1
unnamed: R9.2, U6.13 (FLTN)
unnamed: R26.2, U6.10 (IN+)
unnamed: R42.2, U6.11 (IN-)
unnamed 103: U6.4 (OUTH); also elsewhere on the board
unnamed 104: U6.6 (OUTL); also elsewhere on the board
unnamed: R20.2, U6.12 (RDY)
unnamed: R5.2, U6.14 (RSTN/EN)
unnamed: R48.2, U7.13 (FLTN)
unnamed: R55.2, U7.10 (IN+)
unnamed: R56.2, U7.11 (IN-)
unnamed 110: U7.4 (OUTH); also elsewhere on the board
unnamed 111: U7.6 (OUTL); also elsewhere on the board
unnamed: R49.2, U7.12 (RDY)
unnamed: R47.2, U7.14 (RSTN/EN)
unnamed: R15.2, U10.13 (FLTN)
unnamed: R31.2, U10.10 (IN+)
unnamed: R43.2, U10.11 (IN-)
unnamed 117: U10.4 (OUTH); also elsewhere on the board
unnamed 118: U10.6 (OUTL); also elsewhere on the board
unnamed: R21.2, U10.12 (RDY)
unnamed: R6.2, U10.14 (RSTN/EN)
unnamed: R51.2, U11.13 (FLTN)
unnamed: R57.2, U11.10 (IN+)
unnamed: R58.2, U11.11 (IN-)
unnamed 124: U11.4 (OUTH); also elsewhere on the board
unnamed 125: U11.6 (OUTL); also elsewhere on the board
unnamed: R52.2, U11.12 (RDY)
unnamed: R50.2, U11.14 (RSTN/EN)

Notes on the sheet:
The calculation of the gate resistor is on page 35 ( 9.2.2.5 Turn-On and Turn-Off Gate Resistors)
VCC: 3-5.5V VDD: 13-33 V AIN: 0.6-4.5 APWM D: 88%~10% APWM F: 400kHz APWM bandwidth: 10kHz APWM Duty (%) = -20*V_AIN + 100
for 0805 we can use this: CRCW080510R0FKEAHP
